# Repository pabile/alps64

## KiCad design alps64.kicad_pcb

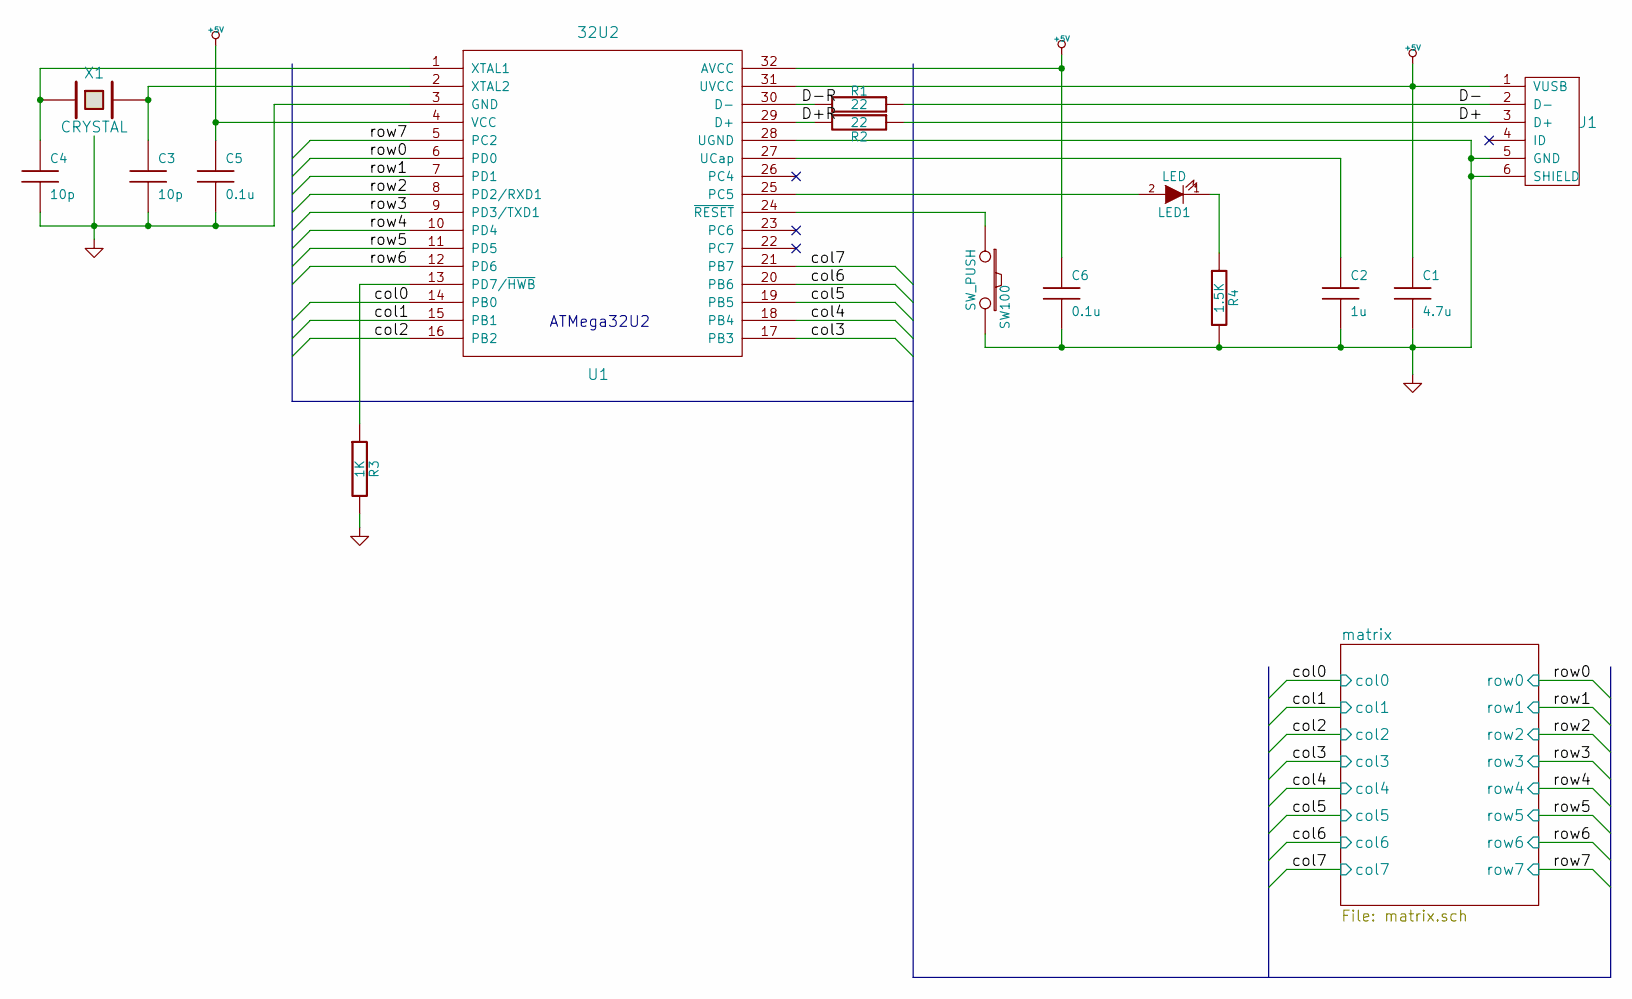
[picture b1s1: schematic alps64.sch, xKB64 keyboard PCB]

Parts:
C1: 4.7u; C_3216
C2: 1u; C_1608
C3, C4: 10p; C_1608
C5, C6: 0.1u; C_1608
J1: USB_mini_micro_B; USB_miniB_hirose_th_reflow
LED1: LED
R1, R2: 22; R_1608
R3: 1K; R_1608
R4: 1.5K; R_1608
SW100: SW_PUSH; SW_ALPS_SKRP
U1: 32U2; QFP32_reflow
X1: CRYSTAL; FA-238

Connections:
+5V: C1.1, C5.1, C6.1, J1.1 (VUSB), U1.4 (VCC), U1.31 (UVCC), U1.32 (AVCC)
/D+: J1.3 (D+), R2.1
/D+R: R2.2, U1.29 (D+)
/D-: J1.2 (D-), R1.1
/D-R: R1.2, U1.30 (D-)
/matrix/col0: U1.14 (PB0); also elsewhere on the board
/matrix/col1: U1.15 (PB1); also elsewhere on the board
/matrix/col2: U1.16 (PB2); also elsewhere on the board
/matrix/col3: U1.17 (PB3); also elsewhere on the board
/matrix/col4: U1.18 (PB4); also elsewhere on the board
/matrix/col5: U1.19 (PB5); also elsewhere on the board
/matrix/col6: U1.20 (PB6); also elsewhere on the board
/matrix/col7: U1.21 (PB7); also elsewhere on the board
/matrix/row0: U1.6 (PD0); also elsewhere on the board
/matrix/row1: U1.7 (PD1); also elsewhere on the board
/matrix/row2: U1.8 (PD2/RXD1); also elsewhere on the board
/matrix/row3: U1.9 (PD3/TXD1); also elsewhere on the board
/matrix/row4: U1.10 (PD4); also elsewhere on the board
/matrix/row5: U1.11 (PD5); also elsewhere on the board
/matrix/row6: U1.12 (PD6); also elsewhere on the board
/matrix/row7: U1.5 (PC2); also elsewhere on the board
GND: C1.2, C2.2, C3.2, C4.2, C5.2, C6.2, J1.5 (GND), J1.6 (SHIELD), R3.2, R4.2, SW100.2, U1.3 (GND), U1.28 (UGND), X1.3
unnamed: C2.1, U1.27 (UCap)
unnamed: C3.1, U1.2 (XTAL2), X1.2
unnamed: C4.1, U1.1 (XTAL1), X1.1
unnamed: LED1.2 (A), U1.25 (PC5)
unnamed: LED1.1 (K), R4.1
unnamed: R3.1, U1.13 (PD7/~HWB)
unnamed: SW100.1, U1.24 (~RESET)

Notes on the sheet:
ATMega32U2

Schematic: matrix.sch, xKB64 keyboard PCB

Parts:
D00, D01, D02, D03, D04, D05, D06, D07, D10, D11, D12, D13, D14, D15, D16, D17, D20, D21, D22, D23, D24, D25, D26, D27, D30, D31, D32, D33, D34, D35, D36, D37, D40, D41, D42, D43, D44, D45, D46, D47, D50, D51, D52, D53, D54, D55, D56, D57, D60, D61, D62, D63, D64, D65, D66, D67, D70, D71, D72, D73, D74, D75, D76, D77: D; D_SOD123_axial
K00, K00_1, K00_2, K00_3, K01, K02, K03, K04, K05, K06, K07, K10, K10_1, K10_2, K11, K12, K13, K14, K15, K16, K17, K20, K20_1, K21, K21_1, K22, K23, K23_1, K24, K24_1, K25, K26, K27, K27_1, K30, K30_1, K31, K31_1, K32, K32_1, K33, K34, K35, K36, K37, K40, K40_1, K40_2, K41, K42, K43, K44, K45, K46, K47, K50, K50_1, K50_2, K51, K52, K53, K54, K55, K56, K57, K60, K60_1, K60_2, K61, K62, K63, K64, K65, K66, K67, K70, K70_1, K71, K72, K73, K74, K75, K76, K77: KEYSW; ALPS_SKCM
K23_2, K23_3: KEYSW

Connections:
/matrix/col0: K00.1, K00_1.1, K00_2.1, K00_3.1, K10.1, K10_1.1, K10_2.1, K20.1, K20_1.1, K30.1, K30_1.1, K40.1, K40_1.1, K40_2.1, K50.1, K50_1.1, K50_2.1, K60.1, K60_1.1, K60_2.1, K70.1, K70_1.1; also elsewhere on the board
/matrix/col1: K01.1, K11.1, K21.1, K21_1.1, K31.1, K31_1.1, K41.1, K51.1, K61.1, K71.1; also elsewhere on the board
/matrix/col2: K02.1, K12.1, K22.1, K32.1, K32_1.1, K42.1, K52.1, K62.1, K72.1; also elsewhere on the board
/matrix/col3: K03.1, K13.1, K23.1, K23_1.1, K23_2.1, K23_3.1, K33.1, K43.1, K53.1, K63.1, K73.1; also elsewhere on the board
/matrix/col4: K04.1, K14.1, K24.1, K24_1.1, K34.1, K44.1, K54.1, K64.1, K74.1; also elsewhere on the board
/matrix/col5: K05.1, K15.1, K25.1, K35.1, K45.1, K55.1, K65.1, K75.1; also elsewhere on the board
/matrix/col6: K06.1, K16.1, K26.1, K36.1, K46.1, K56.1, K66.1, K76.1; also elsewhere on the board
/matrix/col7: K07.1, K17.1, K27.1, K27_1.1, K37.1, K47.1, K57.1, K67.1, K77.1; also elsewhere on the board
/matrix/row0: D00.2, D01.2, D02.2, D03.2, D04.2, D05.2, D06.2, D07.2; also elsewhere on the board
/matrix/row1: D10.2, D11.2, D12.2, D13.2, D14.2, D15.2, D16.2, D17.2; also elsewhere on the board
/matrix/row2: D20.2, D21.2, D22.2, D23.2, D24.2, D25.2, D26.2, D27.2; also elsewhere on the board
/matrix/row3: D30.2, D31.2, D32.2, D33.2, D34.2, D35.2, D36.2, D37.2; also elsewhere on the board
/matrix/row4: D40.2, D41.2, D42.2, D43.2, D44.2, D45.2, D46.2, D47.2; also elsewhere on the board
/matrix/row5: D50.2, D51.2, D52.2, D53.2, D54.2, D55.2, D56.2, D57.2; also elsewhere on the board
/matrix/row6: D60.2, D61.2, D62.2, D63.2, D64.2, D65.2, D66.2, D67.2; also elsewhere on the board
/matrix/row7: D70.2, D71.2, D72.2, D73.2, D74.2, D75.2, D76.2, D77.2; also elsewhere on the board
unnamed 25: D00.1, K00.2, K00_1.2, K00_2.2, K00_3.2; also elsewhere on the board
unnamed: D01.1, K01.2
unnamed: D02.1, K02.2
unnamed: D03.1, K03.2
unnamed: D04.1, K04.2
unnamed: D05.1, K05.2
unnamed: D06.1, K06.2
unnamed: D07.1, K07.2
unnamed 33: D10.1, K10.2, K10_1.2, K10_2.2; also elsewhere on the board
unnamed: D11.1, K11.2
unnamed: D12.1, K12.2
unnamed: D13.1, K13.2
unnamed: D14.1, K14.2
unnamed: D15.1, K15.2
unnamed: D16.1, K16.2
unnamed: D17.1, K17.2
unnamed 41: D20.1, K20.2, K20_1.2; also elsewhere on the board
unnamed: D21.1, K21.2, K21_1.2
unnamed 43: D22.1, K22.2; also elsewhere on the board
unnamed 44: D23.1, K23.2, K23_1.2, K23_2.2, K23_3.2; also elsewhere on the board
unnamed 45: D24.1, K24.2, K24_1.2; also elsewhere on the board
unnamed 46: D25.1, K25.2; also elsewhere on the board
unnamed 47: D26.1, K26.2; also elsewhere on the board
unnamed 48: D27.1, K27.2, K27_1.2; also elsewhere on the board
unnamed 49: D30.1, K30.2, K30_1.2; also elsewhere on the board
unnamed 50: D31.1, K31.2, K31_1.2; also elsewhere on the board
unnamed 51: D32.1, K32.2, K32_1.2; also elsewhere on the board
unnamed: D33.1, K33.2
unnamed: D34.1, K34.2
unnamed: D35.1, K35.2
unnamed 55: D36.1, K36.2; also elsewhere on the board
unnamed: D37.1, K37.2
unnamed: D40.1, K40.2, K40_1.2, K40_2.2
unnamed: D41.1, K41.2
unnamed: D42.1, K42.2
unnamed: D43.1, K43.2
unnamed: D44.1, K44.2
unnamed: D45.1, K45.2
unnamed: D46.1, K46.2
unnamed: D47.1, K47.2
unnamed: D50.1, K50.2, K50_1.2, K50_2.2
unnamed: D51.1, K51.2
unnamed: D52.1, K52.2
unnamed: D53.1, K53.2
unnamed: D54.1, K54.2
unnamed 70: D55.1, K55.2; also elsewhere on the board
unnamed: D56.1, K56.2
unnamed: D57.1, K57.2
unnamed: D60.1, K60.2, K60_1.2, K60_2.2
unnamed: D61.1, K61.2
unnamed: D62.1, K62.2
unnamed 76: D63.1, K63.2; also elsewhere on the board
unnamed: D64.1, K64.2
unnamed 78: D65.1, K65.2; also elsewhere on the board
unnamed: D66.1, K66.2
unnamed: D67.1, K67.2
unnamed 81: D70.1, K70.2, K70_1.2; also elsewhere on the board
unnamed: D71.1, K71.2
unnamed: D72.1, K72.2
unnamed 84: D73.1, K73.2; also elsewhere on the board
unnamed: D74.1, K74.2
unnamed: D75.1, K75.2
unnamed: D76.1, K76.2
unnamed: D77.1, K77.2

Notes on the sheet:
Caps lock
Return
Backslash
Space
Left Gui
Left Control
Right Control
Backspace
Right Alt
Right Gui
App
Left Alt

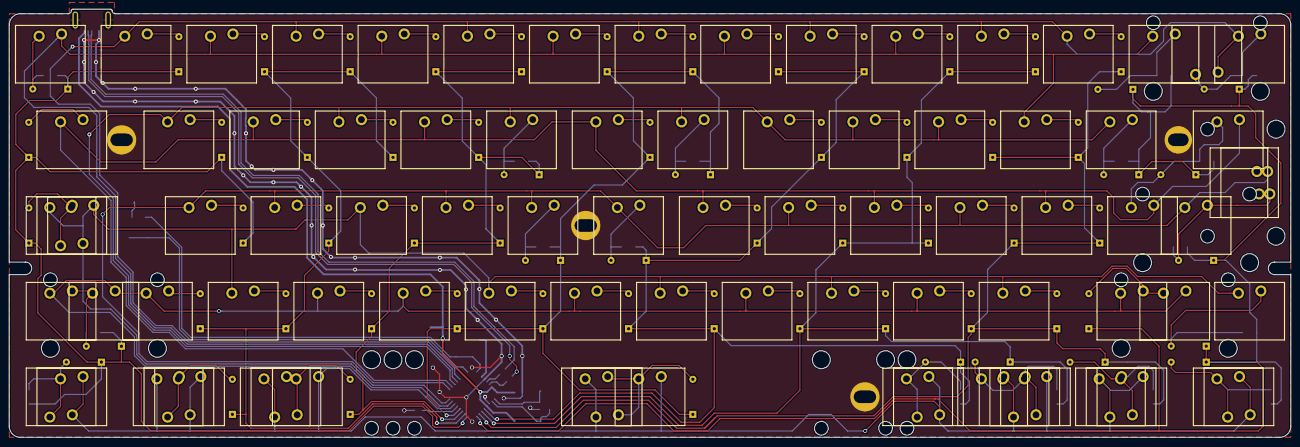
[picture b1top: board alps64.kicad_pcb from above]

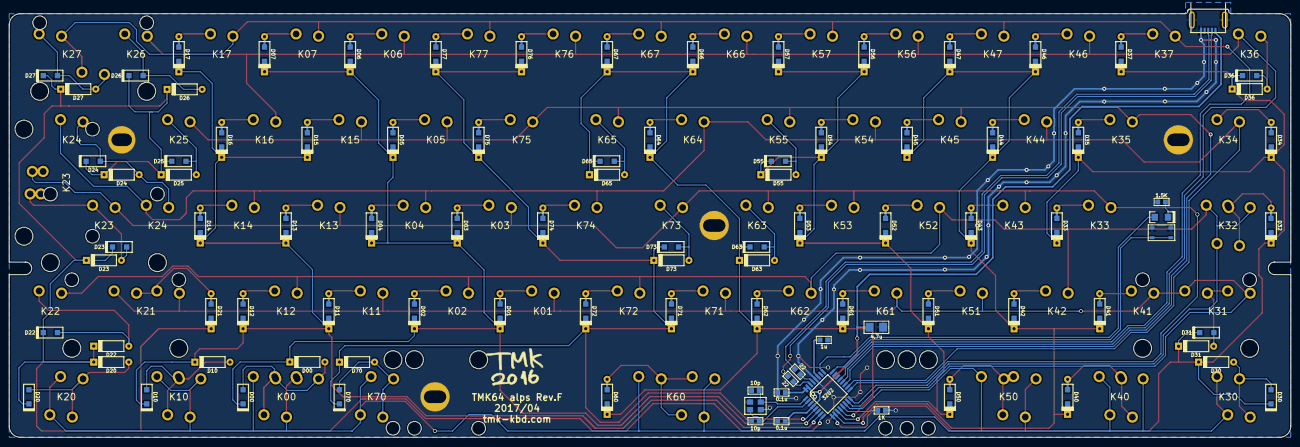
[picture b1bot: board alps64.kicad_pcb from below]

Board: 2 copper layers, 285.0 x 95.2 mm, 199 parts (96 on the bottom side), 93 nets.

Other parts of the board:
Cherry_MX_Stab_2U, Cherry_MX_Stab_2U#2, Cherry_MX_Stab_2U#3, Cherry_MX_Stab_2U#4, Cherry_MX_Stab_2U#5: VAL**; Cherry_MX_Stab_2U
Cherry_MX_Stabilizer: VAL**; Cherry_MX_Stabilizer
Cherry_MX_Stabilizer#2, Cherry_MX_Stabilizer#3, Cherry_MX_Stabilizer#4, Cherry_MX_Stabilizer#5, Cherry_MX_Stabilizer#6: VAL**; Cherry_MX_Stabilizer
D00#2, D20#2, D22#2, D23#2, D24#2, D25#2, D26#2, D27#2, D31#2, D36#2, D55#2, D63#2, D65#2, D73#2: D; D_axial
D10#2, D30#2, D70#2: D; D_SOD123_hand
K32_2: ALPS_SKCM
Poker_oval_hole: VAL**; Poker_oval_hole
Poker_oval_hole#2, Poker_oval_hole#3, Poker_oval_hole#4: VAL**; Poker_oval_hole
Poker_side_edge_long: VAL**; Poker_side_edge_long
Poker_side_edge_long#2: VAL**; Poker_side_edge_long

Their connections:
/matrix/col2: K32_2.1; also elsewhere on the board
/matrix/row0: D00#2.2; also elsewhere on the board
/matrix/row1: D10#2.2; also elsewhere on the board
/matrix/row2: D20#2.2, D22#2.2, D23#2.2, D24#2.2, D25#2.2, D26#2.2, D27#2.2; also elsewhere on the board
/matrix/row3: D30#2.2, D31#2.2, D36#2.2; also elsewhere on the board
/matrix/row5: D55#2.2; also elsewhere on the board
/matrix/row6: D63#2.2, D65#2.2; also elsewhere on the board
/matrix/row7: D70#2.2, D73#2.2; also elsewhere on the board
unnamed 25: D00#2.1; also elsewhere on the board
unnamed 33: D10#2.1; also elsewhere on the board
unnamed 41: D20#2.1; also elsewhere on the board
unnamed 43: D22#2.1; also elsewhere on the board
unnamed 44: D23#2.1; also elsewhere on the board
unnamed 45: D24#2.1; also elsewhere on the board
unnamed 46: D25#2.1; also elsewhere on the board
unnamed 47: D26#2.1; also elsewhere on the board
unnamed 48: D27#2.1; also elsewhere on the board
unnamed 49: D30#2.1; also elsewhere on the board
unnamed 50: D31#2.1; also elsewhere on the board
unnamed 51: K32_2.2; also elsewhere on the board
unnamed 55: D36#2.1; also elsewhere on the board
unnamed 70: D55#2.1; also elsewhere on the board
unnamed 76: D63#2.1; also elsewhere on the board
unnamed 78: D65#2.1; also elsewhere on the board
unnamed 81: D70#2.1; also elsewhere on the board
unnamed 84: D73#2.1; also elsewhere on the board

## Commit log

2017-02-23 Add Cherry MX stab holes
2017-04-09 Reroute for stabs
2017-04-10 Remove excess holes
2017-04-10 Add space stab holes again
2017-04-10 Add stab hole for Enter
